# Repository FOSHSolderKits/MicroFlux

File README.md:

# MicroFlux
Like a microphone, but for magnetic flux.

Based on the idea of the [Elektrosluch](https://store.lom.audio/products/elektrosluch-3?variant=4542168268832).

<a href="https://oshpark.com/shared_projects/lBCzrQec"></img></a>

## Explanation
The explanation of how the circuit works, is annotated in the [schematic](https://github.com/FOSHSolderKits/MicroFlux/blob/master/img/MicroFlux.pdf).

## Pictures

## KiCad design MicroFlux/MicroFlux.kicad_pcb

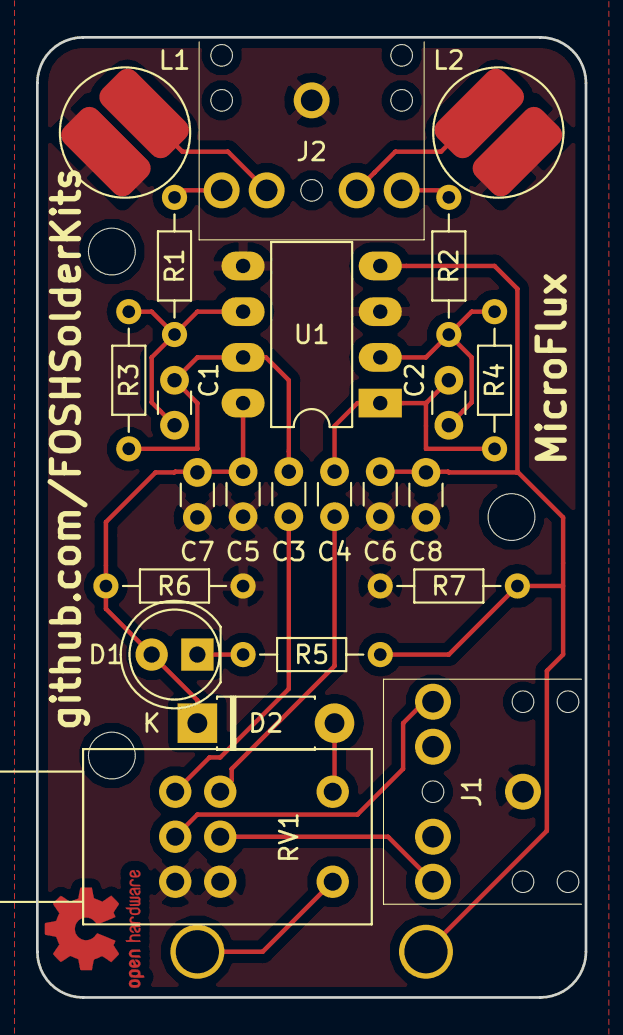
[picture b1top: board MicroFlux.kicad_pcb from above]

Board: 2 copper layers, 30.5 x 53.3 mm, 24 parts (1 on the bottom side), 18 nets.

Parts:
BT1: Battery; BatteryHolder_Eagle_12BH611-GR
C1, C2: 10p; C_Disc_D3.0mm_W1.6mm_P2.50mm
C3, C4, C7, C8: 10u; C_Disc_D3.0mm_W1.6mm_P2.50mm
C5, C6: 100n; C_Disc_D3.0mm_W1.6mm_P2.50mm
D1: green; LED_D5.0mm
D2: 1N5818-T; D_DO-41_SOD81_P7.62mm_Horizontal
J1: Audio Out; 3F07
J2: Audio In; 3F07
L1, L2: 10mH; L_Radial_D7.0mm_P3.00mm
R1, R2: 75; R_Axial_DIN0204_L3.6mm_D1.6mm_P7.62mm_Horizontal
R3, R4: 100k; R_Axial_DIN0204_L3.6mm_D1.6mm_P7.62mm_Horizontal
R5, R6, R7: 1k; R_Axial_DIN0204_L3.6mm_D1.6mm_P7.62mm_Horizontal
RV1: 10k; Potentiometer_Alps_RK097_Dual_Horizontal_Switch
U1: AS358P-E1; DIP-8_W7.62mm_LongPads

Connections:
+BATT: C5.1, C7.1, D1.2, D2.1, R6.1, U1.8
-BATT: BT1.2, C6.2, C8.2, R5.2, R7.2, U1.4
AMPLIFIED_LEFT: C1.1, C3.2, R3.1, U1.7
AMPLIFIED_RIGHT: C2.1, C4.2, R4.1, U1.1
GNDREF: C5.2, C6.1, C7.2, C8.1, J1.S, J2.S, L1.1, L2.1, R6.2, R7.1, RV1.3, RV1.6, U1.3, U1.5
IN_LEFT: J2.T, R1.2
IN_RIGHT: J2.R, R2.2
unnamed: BT1.1, RV1.8
unnamed: C1.2, R1.1, R3.2, U1.6
unnamed: C2.2, R2.1, R4.2, U1.2
unnamed: C3.1, RV1.1
unnamed: C4.1, RV1.4
unnamed: D1.1, R5.1
unnamed: D2.2, RV1.7
unnamed: J1.R, RV1.5
unnamed: J1.T, RV1.2
unnamed: J2.RN, L2.2
unnamed: J2.TN, L1.2

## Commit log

2018-10-14 added hacker ethic
2018-10-18 DRC and List Unconnected passes successfully
2018-10-18 betterplace an route
2018-10-18 render and export images
2018-10-18 schematic plot
2018-10-18 added pictures
2018-10-18 fixed svg links
2018-10-18 added gerber exported files and zip file
2018-10-18 restructured directories
2018-10-18 added OSH Park link
2018-10-18 added logos on board
2018-10-19 assigned MPNs
2018-10-19 exported CSV
2018-10-19 exported pdf
2018-10-19 assigned MPN to OP Amp
2018-10-21 added version information and locked logos on board
2018-10-21 ignore gerber and zip files
2018-10-21 updated OSH Park link in readme
